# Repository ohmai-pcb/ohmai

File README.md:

<!-- SPDX-License-Identifier: Apache-2.0 -->
<!-- Copyright 2026 The OhmAI contributors -->
<picture>
  <source media="(prefers-color-scheme: dark)" srcset="docs/assets/logo/ohmai-logo-dark-transparent.svg">
  <source media="(prefers-color-scheme: light)" srcset="docs/assets/logo/ohmai-logo-light-transparent.svg">
  
</picture>

**Turn a one-line hardware idea into a datasheet-verified, DRC-clean KiCad 9 project — with an AI agent doing the legwork and you in the driver's seat.**

[**Quickstart**](#quickstart) · [**How It Works (The 12 Phases)**](#the-12-phases) · [**What Works Today**](#what-works-today-vs-current-limitations) · [**Layout tools**](#layout-tools) · [**CLI Reference**](#cli-overview) · [**Pinned tools**](#pinned-tool-versions-per-release)

---

### What is OhmAI?

Ask a raw LLM to design a PCB and it will happily hallucinate pin numbers, invent passive values, pick out-of-stock single-source parts, or declare victory with 40 unconnected nets.

**OhmAI** fixes that by giving your coding agent (Cursor, Claude Code, Codex, or any LLM with shell access) a **12-phase hardware engineering harness (`skill/`)** backed by a **deterministic verification CLI (`ohmai`)** for **KiCad 9**:

```bash
ohmai new ~/hw/my-board --anonymous --idea "A solar-powered USB-C charger for 2 phones"
cd ~/hw/my-board && ohmai status
```

Then tell your agent:
> *"My idea is a solar-powered USB-C charger for 2 phones — use OhmAI to make it."*

Your agent researches parts, extracts pin tables and layout rules with exact datasheet page citations, generates hierarchical KiCad 9 schematics, cross-checks multi-source BOM alternates against JLCPCB/LCSC stock, runs `kicad-cli` ERC/DRC and copper-pour checks, and prepares fabrication outputs and bring-up self-test code — pausing at every gate for **independent review** and **your sign-off**.

---

### ✨ Highlights

- 📄 **Zero-Guesswork Datasheet Citations** — Before a single wire is drawn, every IC and connector gets a structured `parts/constraints/<PART>.yaml` where every pin, direction, decoupling rule, and keepout cites an exact PDF page verified against `datasheets/manifest.yaml`.
- 🔍 **Deterministic KiCad 9 & Netlist Checks** — `ohmai check <phase> --gate` wraps `kicad-cli` (ERC, DRC, Gerber/drill/3D export), diffs your schematic netlist against `expected_nets.csv`, and verifies voltage dividers, capacitor DC-bias derating, I²C pull-ups, critical switching loops, and copper pour neck widths.
- 🛡️ **3-Rule BOM Sourcing & `jlcparts` Verification** — Automatically enforces multi-manufacturer drop-in alternates, cross-checks every LCSC `C#` code and package against an offline `jlcparts` database, and flags any single-source component until rejected alternatives and an owner decision (`D-xxx`) are documented.
- 🤝 **Multi-Agent Independent Review Gates** — Built-in review briefs (`ohmai review start <phase>`) require a separate reviewer identity (a second model, reviewer agent, or human engineer — never the authoring session) locked to a cryptographic `files_hash`.
- 🧪 **Ready-to-Run Bring-Up Code & Compliance Docs** — Generates pre-board bench test plans, target-market safety/compliance manuals (`CE` / `FCC` / `WEEE`), and self-test firmware verified against `hardware/gen/pinmap.yaml` before you ever power on a board.

---

Plugin/skill installation for Cursor, Grok Build, Grok Bot and Claude Code: [INSTALL.md](INSTALL.md). The prepared 0.2.0 plugin is guidance only; external tools are separate.

## Why OhmAI exists

Left to their own devices on a PCB project, LLM agents tend to guess pin numbers, invent passive values, pick single-source parts that are out of stock, or declare victory while DRC has dozens of unconnected nets.

OhmAI does **not** make an LLM an autonomous senior hardware engineer. Instead, it constrains the agent inside a 12-phase gated workflow where claims must be backed by deterministic CLI checks and cited datasheet pages, and where the human owner makes every architectural, component, and waiver decision:

- **The owner decides; agents do the legwork.** Nothing locks without human sign-off (`docs/decisions.md` + `STATUS.md`). In practice, the human owner still steers trade-offs, catches bad physical assumptions, and decides when a layout or sourcing compromise is acceptable.
- **Datasheet-cited constraints (`parts/constraints/<PART>.yaml`).** Before drawing a schematic, every IC and connector gets a structured YAML file listing pins, directions, decoupling rules, and layout constraints — each citing a page number verified against `datasheets/manifest.yaml`. Pin directions are never guessed.
- **Deterministic checks (`ohmai check <phase> --gate`).** Wraps `kicad-cli` (sheet load, ERC, DRC, Gerber/drill/3D export), diffs the schematic netlist against `expected_nets.csv`, checks pin maps, regulator outputs, passive values, I²C pull-ups, copper pour continuity, and BOM-to-fab parity.
- **Independent review gates (`ohmai review start <phase>`).** Line-by-line review gates (`safety`, `constraints`, `schematic`, `layout`, `bom`, `fab`, `bringup`) require a separate reviewer identity (another model/vendor, a separate reviewer agent, or a human — never the authoring session) bound to a SHA-256 `files_hash`.
- **Git is the memory.** Approved state, open questions, review resolutions, and waivers live in the repository so any agent or human can inspect or resume the project.

---

## What works today vs. current limitations

> **Status: v0.2 (unreleased, experimental / early-stage).** Layout tooling, plugin packaging and release prep are in tree but not tagged. No public example board or physical fabrication is claimed. See [ROADMAP](docs/ROADMAP.md).

### Works well today
- **Datasheet constraint extraction & citation checking (`ohmai check constraints`, `ohmai datasheets`):** Catching pinout/direction mistakes, missing pull-ups, and unverified datasheet claims before schematic capture begins. Tracking datasheet URLs, SHA-256 digests, and cited pages in `datasheets/manifest.yaml` without committing binary `.pdf` blobs.
- **Schematic, netlist, and BOM parity (`ohmai check schematic`, `ohmai check bom`):** Enforcing 1:1 parity across `expected_nets.csv`, `hardware/*.kicad_sch`, `hardware/*.kicad_pcb`, `hardware/gen/pinmap.yaml`, and `bom/bom.csv`.
- **3-rule BOM sourcing & `jlcparts` verification:** Requiring multi-manufacturer alternates for passives and active parts (or an explicit `single-source:` justification listing `checked:` rejected candidates + owner decision `D-xxx`), cross-checked against a local `jlcparts` SQLite database (`OHMAI_JLCPARTS_DB`).
- **Pre-board bring-up self-test & manual checks (`ohmai check bringup-code`, `ohmai check manual`):** Verifying that bring-up test scripts use the exact GPIO assignments in `hardware/gen/pinmap.yaml` and that `docs/manual.md` covers all `MW-xx` warnings and target-market compliance sections.

### Still rough / requires heavy human steering
- **PCB placement and routing (`ohmai layout`):** The 4-stage layout pipeline (`fit`, `fanout`, `autoroute` via Freerouting, `handroute`, `pour`) and `ohmai check placement` (`critical_loops` and `keepouts`) can close a dense board to `0` DRC violations and `0` unconnected nets, **but the resulting copper looks like an autorouter output plus scripted patch routes — not a clean, human-crafted PCB layout.** Closing tight boards in v0.1 required human guidance, iterative placement adjustments, passive package swaps (`0603` → `0402`), and explicit owner waivers (such as allowing signal hops on an internal power plane).
- **Reference-level complexity so far:** v0.1 has been exercised on datasheet-application-note circuits (MCU + buck-boost SMPS + SPI sensor front end), not high-speed impedance-controlled, RF, or high-voltage designs.

---

## Layout tools

The 4-stage layout pipeline (`fit`, `fanout`, `autoroute`, `handroute`, `pour`) is documented in [docs/LAYOUT.md](docs/LAYOUT.md). When to use OhmAI handroute versus Freerouting: [docs/routing/ROUTER-GUIDE.md](docs/routing/ROUTER-GUIDE.md).

- **`ohmai layout apply-changes`** — versioned board edits, including copper-zone add, resize and delete, with dry-run, refill, DRC gate and rollback.
- **`ohmai layout zones`** — list zones with a ready `expect` block for change lists.
- **`ohmai layout current`** — IPC-2152 (or legacy IPC-2221) screening of current targets against copper weight and temperature rise; reports width, pour-neck pass/fail and stitching-via count.
- **`ohmai layout pour --board` / `--section` / `--width-at`** — plane continuity and width reports on a chosen board or cut line.
- **`ohmai layout handroute`** — bounded router for power, high-current and custom-rule nets; island counts are intended to match KiCad.
- **`ohmai layout autoroute`** — Freerouting 2.5.0 (jar + JDK 25) as a staged subprocess, scoped with `--nets` / `--exclude-nets`. An SES is not a DRC pass.

Closing a dense board still needs human steering. The copper often looks like an autorouter output plus scripted patch routes, not a clean hand-crafted layout.

## Example projects

These boards are being prepared as public examples. They are not published yet, so this list has no links.

- pico-k
- usb-c-12v-stereo
- hohme-sense

---

## The 12 Phases

| # | Phase (`<id>`) | Outputs | Automated Checks & Review Gate | Gate (Human Owner) |
|---|---|---|---|---|
| 1 | `requirements` | `docs/requirements.md` (`R-xx` specs, tolerances, markets, size/cost targets) | `status`, `questions`, `commits` | Locks the spec |
| 2 | `architecture` | `docs/architecture.md` (options, block diagram, trade study) | `status`, `questions`, `commits` | Picks an option |
| 3 | `safety` | `docs/safety.md` (applicable directives per market, `MW-xx` manual warnings) | `safety`, `review:safety` | Approves compliance plan before parts freeze |
| 4 | `parts` | `parts/selection.md`, initial `bom/bom.csv`, `datasheets/manifest.yaml` | `bom` (3-rule sourcing & `jlcparts`), `datasheets` | Approves parts & alternates |
| 5 | `constraints` | `parts/constraints/<PART>.yaml` + `expected_nets.csv` | `constraints` (page citations, pin tables), `review:constraints` | Approves after independent review |
| 6 | `rfq` | `parts/rfq/` supplier questions / RFQs (or N/A) | `status`, `questions`, `commits` | Sends RFQs (or marks N/A) |
| 7 | `schematic` | Hierarchical KiCad 9 schematics (`hardware/*.kicad_sch`), `hardware/gen/pinmap.yaml` | `toolchain`, `kicad-libs`, `sheet-load`, `erc`, `netlist-diff`, `pinmap`, `power`, `passives`, `buses`, `readability`, `renders`, `review:schematic` | Reviews schematic diff, renders & netlist parity |
| 8 | `layout` | `hardware/<project>.kicad_pcb`, 2D/3D renders, `docs/layout/checklist.md` | `drc`, `placement` (`critical_loops` & `keepouts`), `renders`, `models-3d`, `review:layout` | Reviews 2D/3D layout, pour continuity & waivers |
| 9 | `enclosure` | `docs/enclosure.md`, exported board `.step` (or N/A) | `status`, `questions`, `commits` | Approves mechanical fit (or N/A) |
| 10 | `bom` | Locked `bom/bom.csv`, optional `bom/fab-actual.csv` diff | `bom`, `review:bom` | Locks the BOM |
| 11 | `fab` | Gerbers, drills, PnP (`cpl.csv`), assembly BOM (`out/fab/<rev>/`) | `fab` (re-runs 7+8+10 + Gerber/drill/CPL export), `review:fab` (`require_kind: human`) | Human pre-order sign-off; tags `rev-A` |
| 12 | `bringup` | `test/bringup-plan.md`, `test/firmware/bringup_selftest.*`, `docs/manual.md` | `bringup-code`, `manual`, `review:bringup` (`require_kind: human`) | Human sign-off on real hardware measurements |

Details: [`skill/phases/`](skill/phases/), [`docs/ARCHITECTURE.md`](docs/ARCHITECTURE.md), and [`docs/REVIEWS.md`](docs/REVIEWS.md).

---

## Quickstart

### Requirements
- **Python ≥ 3.10**, **git**, and **KiCad 9.0.x** (`kicad-cli` on `PATH`; this release was tested with 9.0.2). KiCad checks report `SKIP` without it.
- Shared or ephemeral agent boxes: restore with `scripts/restore-toolchain.sh` (pinned KiCad + durable `~/ohmai-venv` + `ohmai setup`, HTTPS-mirror fallback, single-installer lock); see [docs/TOOLCHAIN.md](docs/TOOLCHAIN.md).
- External tools this release pins (see [Pinned tool versions per release](#pinned-tool-versions-per-release)): Freerouting 2.5.0 (jar + JDK 25) and easyeda2kicad 1.0.1, plus optional `rsvg-convert` (`librsvg2-bin`) and a local `jlcparts` SQLite database (`OHMAI_JLCPARTS_DB` or `~/.cache/ohmai/jlcparts/cache.sqlite3`).

### Install & Create a Project
```bash
pip install "git+https://github.com/ohmai-pcb/ohmai.git@v0.2.0#subdirectory=cli"   # v0.2.0 tag is created at release; before that, install from a checkout (next line)
# contributors: git clone https://github.com/ohmai-pcb/ohmai.git && cd ohmai && pip install -e "cli[dev,layout]"
ohmai setup                            # install this release's pinned tools (no prompts)
ohmai skill install                    # copies skill/ to ~/.cursor/skills/ohmai (use --dest for other agents)

# Create a new project (add --anonymous for clean public repos using role labels & repo-relative paths)
ohmai new ~/hw/my-board --anonymous --idea "A solar-powered USB-C charger for 2 phones"
cd ~/hw/my-board && ohmai status && ohmai check current
```

Then tell your agent: *"My idea is a solar-powered USB-C charger for 2 phones, use OhmAI to make it."* The agent follows [`skill/SKILL.md`](skill/SKILL.md).

---

## CLI Overview

| Command | Purpose |
|---|---|
| `ohmai new <path> --idea "..." [--anonymous] [--github OWNER/NAME]` | Initialize a project repo from `template/`, pin `.ohmai/phases/`, and install git hooks. `--github` prints the exact `gh repo create` command (private by default) and runs it only after an interactive y/N confirm or `--yes` |
| `ohmai status [--set-phase N --gate G --decision D-xxx]` | Show current phase, gate status, locked decisions, and open questions; set phase/gate in STATUS.md front matter |
| `ohmai check [current\|<phase>\|<check>] [--gate]` | Run deterministic checks (`--list` to view all checks); writes `out/summary.md` |
| `ohmai review start <phase>` | Generate `reviews/<phase>/BRIEF.md` (with SHA-256 `files_hash`) and `resolutions.md` |
| `ohmai layout {fit,fanout,autoroute,pour,handroute,zones,current,apply-changes}` | 4-stage layout helpers, zone list/edit, current sizing; autoroute is Freerouting 2.5.0 with `--nets` / `--exclude-nets`. See [docs/LAYOUT.md](docs/LAYOUT.md) |
| `ohmai passives swap <REF> --package <0402\|0603\|0805>` | Swap a passive package across schematic/layout specs while keeping BOM parity |
| `ohmai datasheets {manifest,fetch,check}` | Manage `datasheets/manifest.yaml` (SHA-256 digests + cited pages) and fetch PDFs on demand |
| `ohmai kicad-libs {install,tables,models,status}` | Manage pinned KiCad libraries and fetch/generate project-scoped 3D `.step` models |
| `ohmai kicad-libs {fetch,import,verify,list} <MPN>` | Agent-only fetch/import of parts the pinned libraries lack (LCSC/EasyEDA via easyeda2kicad, direct manufacturer URL) into `hardware/lib/` + lib tables + `manifest.yaml`, datasheet pin check and pin types; walled sources exit 75 |
| `ohmai commit -m "..." [-a]` / `ohmai hooks {install,status}` | Commit with `OhmAI-Author:` trailers and manage `commit-msg` / `pre-push` hooks |
| `ohmai setup` / `ohmai doctor` | Install and verify this release's pinned tools (`pinned-tools.yaml`); doctor also checks git hooks |
| `ohmai lock` / `ohmai upgrade` / `ohmai release <tag>` | Manage `toolchain.lock.yaml` or build a fabrication release (`--dry-run` supported) |
| `ohmai golden` / `ohmai known-bad` | Run golden reference projects and the planted-bug mutation fixtures (`tests/fixtures/known-bad/`) |

---

## Repo Layout

```text
skill/            SKILL.md (agent entry point) + phases/01..12.md
template/         Project skeleton copied by `ohmai new` (AGENTS.md, STATUS.md, ohmai.yaml, docs/, parts/, hardware/, bom/)
cli/              Python package (`ohmai`): CLI commands, checks, layout helpers, review & datasheet manifest tools
tests/            known-bad mutation fixtures (one planted bug per check) and golden reference projects
scripts/          canary.py (newest KiCad/libs vs the suites), pylock.py
docs/             ARCHITECTURE.md, LAYOUT.md, REVIEWS.md, ROADMAP.md, TESTING.md, assets/logo/, routing/
```

---

## Pinned tool versions per release

Each ohmai release ships `pinned-tools.yaml` with the exact external tool versions it was
tested with. `ohmai setup` installs those versions with no questions and verifies
checksums; `ohmai doctor` FAILs on a mismatch and prints the expected version, the found
version, and the fix. Set `OHMAI_ALLOW_UNPINNED=1` (or `toolchain.allow_unpinned: true` in
a project) to downgrade a mismatch to a warning when you are testing a newer tool.

This release pins:

| Tool | Pin |
|---|---|
| Freerouting | 2.5.0 jar (GitHub release URL + sha256); use the jar with JDK 25, not the GraalVM native CLI. `ohmai layout autoroute` always passes `--user_data_path` under `~/.local/share/ohmai/freerouting/<ver>/userdata` so the shared `~/.config/freerouting` is never touched. |
| JDK | 25 (major; any 25.x build). Auto-discovered from `~/.local/share/jdk25`, the ohmai cache, or `OHMAI_JDK_ROOT` (an optional extra search root); `FREEROUTING_JAVA` remains an override. |
| KiCad (`kicad-cli`) | 9.0.2 tested; accepted range `9.0.x` |
| easyeda2kicad | 1.0.1 (PyPI, AGPL-3.0, subprocess only) |

A project's `toolchain.lock.yaml` is separate: it records the tools that design was built
with. Before tagging a release, bump the pins and re-run the suite plus the Freerouting
smoke test (see [docs/TESTING.md](docs/TESTING.md)).

## License

Apache-2.0 (see [LICENSE](LICENSE) and [NOTICE](NOTICE)). Copyright 2026 The OhmAI contributors. GPL/AGPL tools (`kicad-cli`/pcbnew, Freerouting, easyeda2kicad, KiBot, SKiDL) are invoked as separate external processes and are never vendored or imported. `ohmai setup` may install easyeda2kicad (AGPL-3.0) and the Freerouting jar (GPL-3.0) as separate programs; downloads from EasyEDA follow EasyEDA's terms. Projects you generate with `ohmai new` are yours.

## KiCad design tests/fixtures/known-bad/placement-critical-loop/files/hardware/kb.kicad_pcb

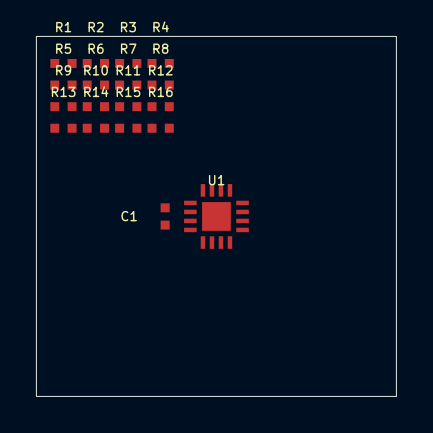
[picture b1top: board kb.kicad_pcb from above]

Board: 2 copper layers, 20.0 x 20.0 mm, 18 parts (0 on the bottom side), 17 nets, no tracks yet.

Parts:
C1: C_fixture
R1, R2, R3, R4, R5, R6, R7, R8, R9, R10, R11, R12, R13, R14, R15, R16: C_fixture
U1: QFN-16_fixture

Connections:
/S1: R1.1, U1.1
/S2: C1.1, R2.1, U1.2
/S3: R3.1, U1.3
/S4: R4.1, U1.4
/S5: R5.1, U1.5
/S6: R6.1, U1.6
/S7: R7.1, U1.7
/S8: R8.1, U1.8
/S9: R9.1, U1.9
/S10: R10.1, U1.10
/S11: R11.1, U1.11
/S12: R12.1, U1.12
/S13: R13.1, U1.13
/S14: R14.1, U1.14
/S15: R15.1, U1.15
/S16: R16.1, U1.16
GND: C1.2, R1.2, R2.2, R3.2, R4.2, R5.2, R6.2, R7.2, R8.2, R9.2, R10.2, R11.2, R12.2, R13.2, R14.2, R15.2, R16.2, U1.17
